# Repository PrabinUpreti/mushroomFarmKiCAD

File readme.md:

Hello this Is PCB Design Repo. Using kiCAD

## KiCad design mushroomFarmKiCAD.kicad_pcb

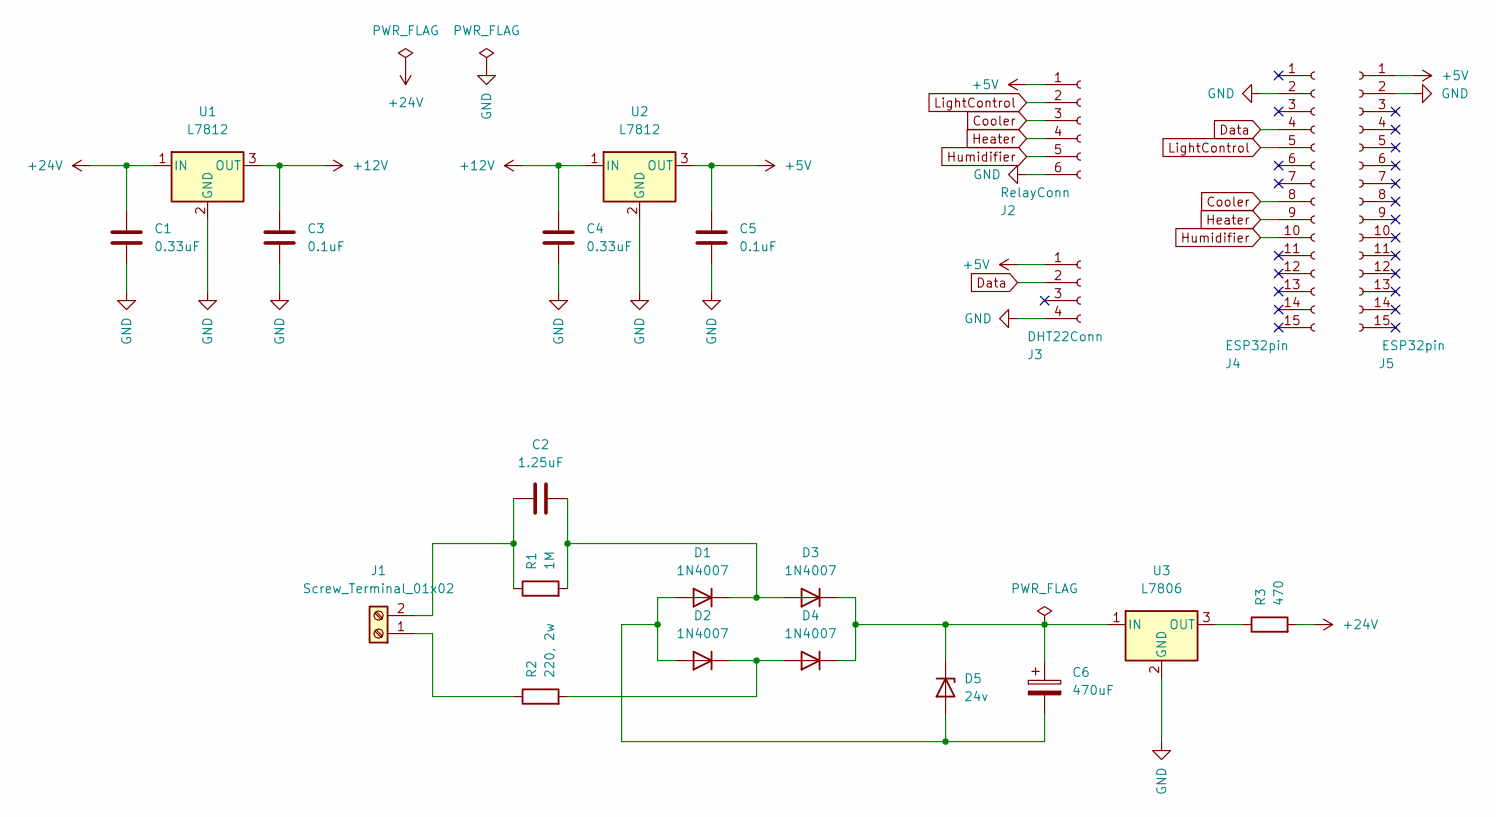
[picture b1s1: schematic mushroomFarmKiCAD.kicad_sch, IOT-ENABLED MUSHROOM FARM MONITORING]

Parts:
C1: 0.33uF; CP_Radial_D8.0mm_P3.80mm
C2: 1.25uF; C_Disc_D16.0mm_W5.0mm_P10.00mm
C3, C5: 0.1uF; CP_Radial_D10.0mm_P5.00mm
C4: 0.33uF; CP_Radial_D10.0mm_P5.00mm
C6: 470uF; CP_Radial_D10.0mm_P5.00mm
D1, D2, D3, D4: 1N4007; D_DO-41_SOD81_P10.16mm_Horizontal
D5: 24v; D_DO-41_SOD81_P10.16mm_Horizontal
J1: Screw_Terminal_01x02; TerminalBlock_Phoenix_MKDS-1,5-2_1x02_P5.00mm_Horizontal
J2: RelayConn; PinSocket_1x06_P2.54mm_Vertical
J3: DHT22Conn; PinSocket_1x04_P2.54mm_Vertical
J4, J5: ESP32pin; PinSocket_1x15_P2.54mm_Vertical
R1: 1M; R_Axial_DIN0411_L9.9mm_D3.6mm_P12.70mm_Horizontal
R2: 220, 2w; R_Axial_DIN0411_L9.9mm_D3.6mm_P12.70mm_Horizontal
R3: 470; R_Axial_DIN0411_L9.9mm_D3.6mm_P12.70mm_Horizontal
U1, U2: L7812; TO-262-3_Vertical
U3: L7806; TO-262-3_Vertical

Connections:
+5V: C5.1, J2.1, J3.1, J5.1, U2.3 (OUT)
+12V: C3.1, C4.1, U1.3 (OUT), U2.1 (IN)
+24V: C1.1, R3.2, U1.1 (IN)
Cooler: J2.3, J4.8
Data: J3.2, J4.4
GND: C1.2, C3.2, C4.2, C5.2, J2.6, J3.4, J4.2, J5.2, U1.2 (GND), U2.2 (GND), U3.2 (GND)
Heater: J2.4, J4.9
Humidifier: J2.5, J4.10
LightControl: J2.2, J4.5
unnamed: C2.1, J1.2, R1.1
unnamed: C2.2, D1.1 (K), D3.2 (A), R1.2
unnamed: C6.1, D3.1 (K), D4.1 (K), D5.1 (K), U3.1 (IN)
unnamed: C6.2, D1.2 (A), D2.2 (A), D5.2 (A)
unnamed: D2.1 (K), D4.2 (A), R2.2
unnamed: J1.1, R2.1
unnamed: R3.1, U3.3 (OUT)

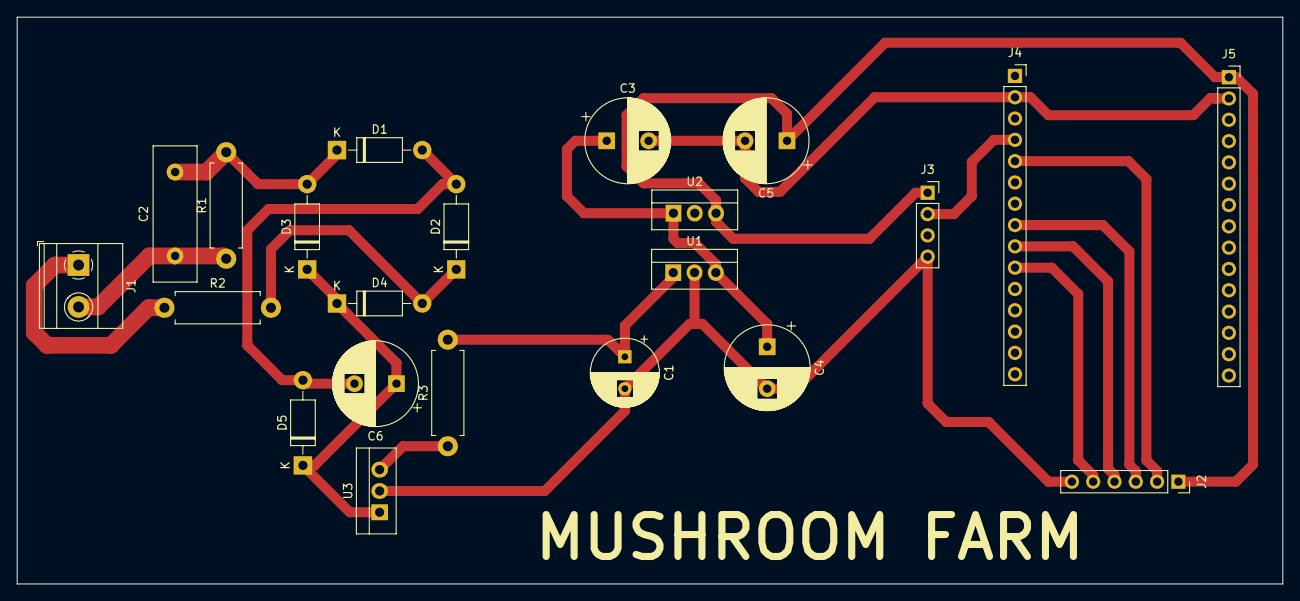
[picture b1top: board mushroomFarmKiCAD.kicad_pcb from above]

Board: 2 copper layers, 150.9 x 67.6 mm, 22 parts (0 on the bottom side), 16 nets.

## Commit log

2022-12-14 design circuit with wire and finalize schematic
2022-12-15 Created PCB added 3d models, improve pcb
